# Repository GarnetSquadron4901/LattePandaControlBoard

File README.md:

# LattePanda FRC Driver Station
This is Garnet Squadron's next iteration to the control board. This one dumps the typical laptop and opts for a LattePanda Windows 10 single-board computer with Arduino Leonardo Co-Processor. This repo will hold Windows software, Arduino firmware, design files, and documentation.

## Features
- 16 20mA LED Outputs
- 16 General Purpose I/O
- 16 Analog Inputs
- 16 PWM Outputs
- Backup battery for safe shutdowns
- Auto power-on with AC connect
- LattePanda 
	- Windows 10 Professional
	- 4GB RAM
	- 64GB SSD
	- Intel Cherry Trail Z8300 Quad Core 1.8GHz
	- 3 USB Ports (2 USB 2.0, 1 USB 3.0)
	- Ethernet 10/100
	- 7" Capacitive Touch Screen (1024 x 600)
	- WiFi
	- Bluetooth

## How it works
The Arduino Leondaro connects with I/O expansion chips:

- Microchip MCP23017 - 16-Bit GPIO Expander with I2C Interface
- NXP PCA9685 - 16 channel PWM Driver
- TI CD74HC4067 Analog Multiplexer
- TI TLC59282 16-Channel Constant-Current LED Driver

There is a 2000 mAh LiPo battery that can provide backup power for an estimated 1 hour. While the battery life isn't great, the intended purpose is to provide power long enough to shutdown Windows 10 between matches. Override inputs will be available to:

- Keep the board powered on until battery life reaches ~5%
- Power button to turn on the system even when off of AC power.

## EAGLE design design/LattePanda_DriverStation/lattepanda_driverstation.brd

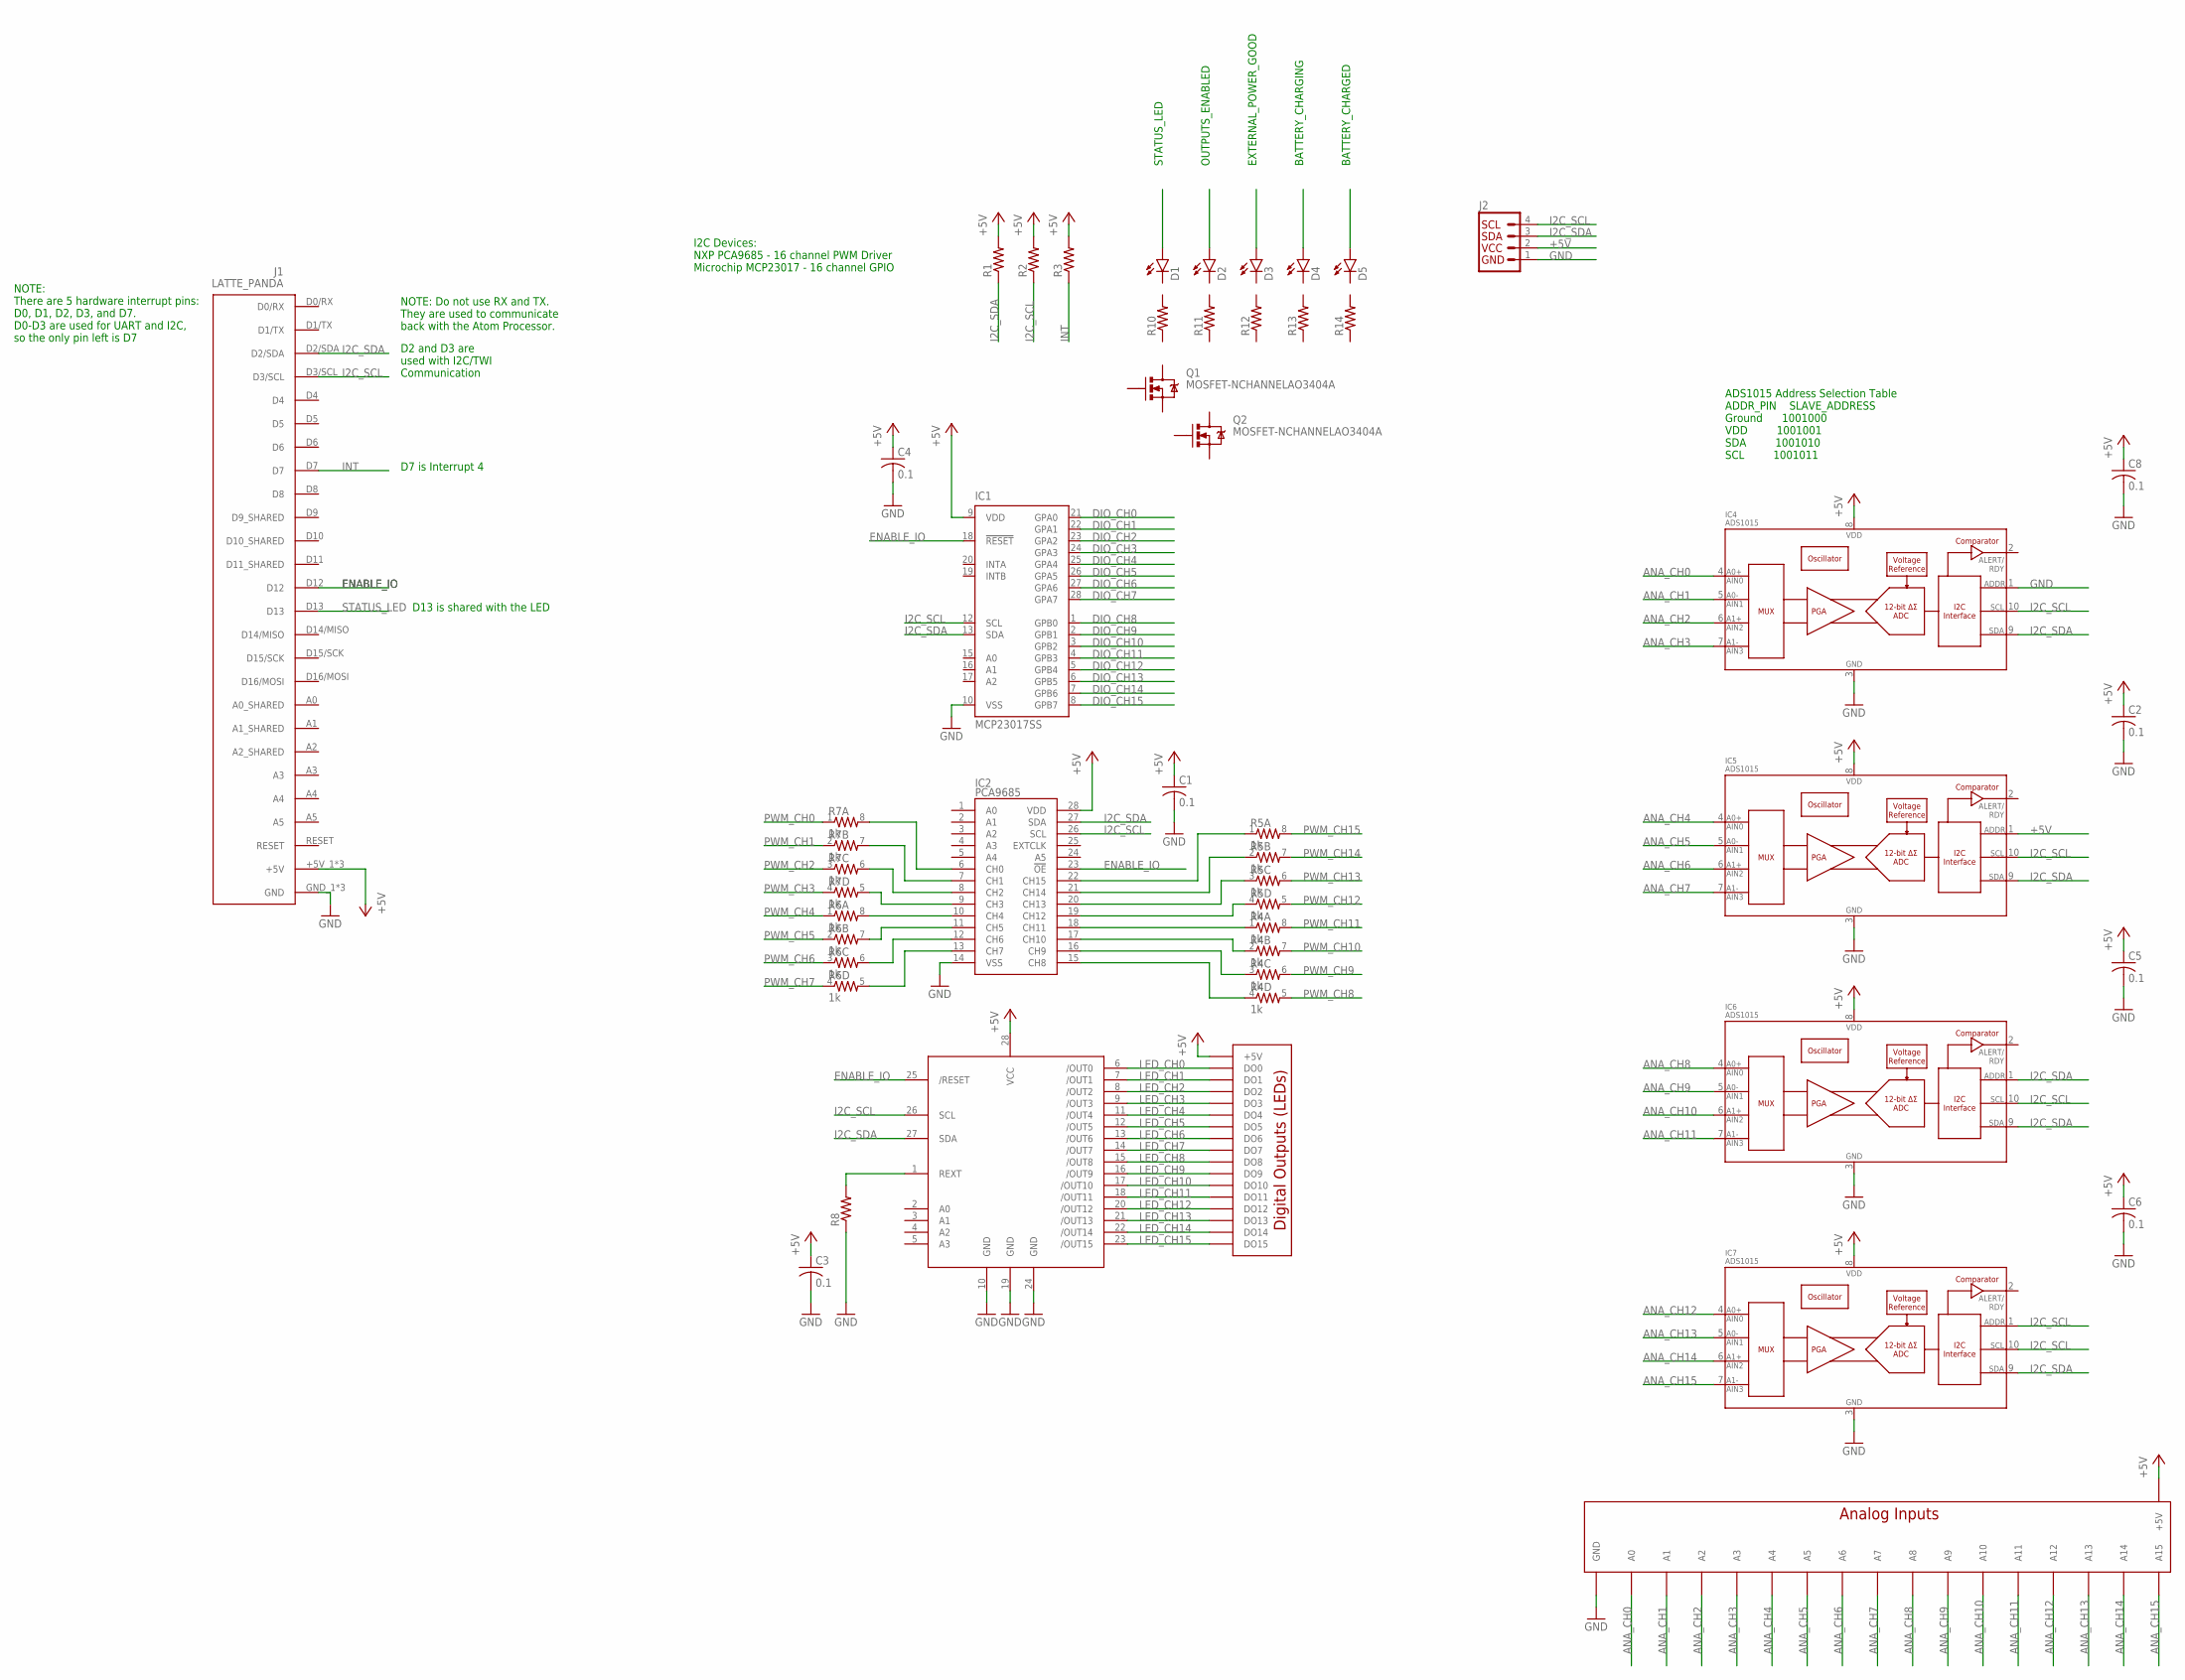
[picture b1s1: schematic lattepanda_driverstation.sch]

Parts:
C1, C2, C3, C4, C5, C6, C8: 0.1; C1206
D1, D2, D3, D4, D5: LED1206; LED-1206
IC1: MCP23017SS; SSOP28
IC2: PCA9685; TSSOP-28_4MM
IC3: TLC59116; TSSOP28
IC4, IC5, IC6, IC7: ADS1015; MSOP10
J1: LATTE_PANDA
J2: I2C_STANDARD; 1X04
Q1, Q2: MOSFET-NCHANNELAO3404A; SOT23-3
R1, R2, R3, R10, R11, R12, R13, R14: R-US_M1206; M1206
R4, R5, R6, R7: 1k; 0603-ARV
R8: R-US_R1206; R1206
U$1: ANALOGHEADER
U$2: DIGITALOUTPUTS; DIGITALOUT

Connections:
+5V: C1.1, C2.1, C3.1, C4.1, C5.1, C6.1, C8.1, IC1.9 (VDD), IC2.28 (VDD), IC3.28 (VCC), IC4.8 (VDD), IC5.1 (ADDR), IC5.8 (VDD), IC6.8 (VDD), IC7.8 (VDD), J1.+5V_1 (+5V), J1.+5V_2 (+5V), J1.+5V_3 (+5V), J2.2, R1.2, R2.2, R3.2, U$1.+5V@0 (+5V), U$1.+5V@1 (+5V), U$1.+5V@2 (+5V), U$1.+5V@3 (+5V), U$1.+5V@4 (+5V), U$1.+5V@5 (+5V), U$1.+5V@6 (+5V), U$1.+5V@7 (+5V), U$1.+5V@8 (+5V), U$1.+5V@9 (+5V), U$1.+5V@10 (+5V), U$1.+5V@11 (+5V), U$1.+5V@12 (+5V), U$1.+5V@13 (+5V), U$1.+5V@14 (+5V), U$1.+5V@15 (+5V), U$2.+5V@0 (+5V), U$2.+5V@1 (+5V), U$2.+5V@2 (+5V), U$2.+5V@3 (+5V), U$2.+5V@4 (+5V), U$2.+5V@5 (+5V), U$2.+5V@6 (+5V), U$2.+5V@7 (+5V), U$2.+5V@8 (+5V), U$2.+5V@9 (+5V), U$2.+5V@10 (+5V), U$2.+5V@11 (+5V), U$2.+5V@12 (+5V), U$2.+5V@13 (+5V), U$2.+5V@14 (+5V), U$2.+5V@15 (+5V)
ANA_CH0: IC4.4 (AIN0), U$1.0 (A0)
ANA_CH1: IC4.5 (AIN1), U$1.1 (A1)
ANA_CH2: IC4.6 (AIN2), U$1.2 (A2)
ANA_CH3: IC4.7 (AIN3), U$1.3 (A3)
ANA_CH4: IC5.4 (AIN0), U$1.4 (A4)
ANA_CH5: IC5.5 (AIN1), U$1.5 (A5)
ANA_CH6: IC5.6 (AIN2), U$1.6 (A6)
ANA_CH7: IC5.7 (AIN3), U$1.7 (A7)
ANA_CH8: IC6.4 (AIN0), U$1.8 (A8)
ANA_CH9: IC6.5 (AIN1), U$1.9 (A9)
ANA_CH10: IC6.6 (AIN2), U$1.10 (A10)
ANA_CH11: IC6.7 (AIN3), U$1.11 (A11)
ANA_CH12: IC7.4 (AIN0), U$1.12 (A12)
ANA_CH13: IC7.5 (AIN1), U$1.13 (A13)
ANA_CH14: IC7.6 (AIN2), U$1.14 (A14)
ANA_CH15: IC7.7 (AIN3), U$1.15 (A15)
DIO_CH0: IC1.21 (GPA0)
DIO_CH1: IC1.22 (GPA1)
DIO_CH2: IC1.23 (GPA2)
DIO_CH3: IC1.24 (GPA3)
DIO_CH4: IC1.25 (GPA4)
DIO_CH5: IC1.26 (GPA5)
DIO_CH6: IC1.27 (GPA6)
DIO_CH7: IC1.28 (GPA7)
DIO_CH8: IC1.1 (GPB0)
DIO_CH9: IC1.2 (GPB1)
DIO_CH10: IC1.3 (GPB2)
DIO_CH11: IC1.4 (GPB3)
DIO_CH12: IC1.5 (GPB4)
DIO_CH13: IC1.6 (GPB5)
DIO_CH14: IC1.7 (GPB6)
DIO_CH15: IC1.8 (GPB7)
ENABLE_IO: IC1.18 (!RESET), IC2.23 (!OE), IC3.25 (/RESET), J1.D12
GND: C1.2, C2.2, C3.2, C4.2, C5.2, C6.2, C8.2, IC1.10 (VSS), IC2.14 (VSS), IC3.10 (GND), IC3.19 (GND), IC3.24 (GND), IC4.1 (ADDR), IC4.3 (VSS), IC5.3 (VSS), IC6.3 (VSS), IC7.3 (VSS), J1.GND_1 (GND), J1.GND_2 (GND), J1.GND_3 (GND), J2.1, R8.1, U$1.GND@0 (GND), U$1.GND@1 (GND), U$1.GND@2 (GND), U$1.GND@3 (GND), U$1.GND@4 (GND), U$1.GND@5 (GND), U$1.GND@6 (GND), U$1.GND@7 (GND), U$1.GND@8 (GND), U$1.GND@9 (GND), U$1.GND@10 (GND), U$1.GND@11 (GND), U$1.GND@12 (GND), U$1.GND@13 (GND), U$1.GND@14 (GND), U$1.GND@15 (GND)
I2C_SCL: IC1.12 (SCL), IC2.26 (SCL), IC3.26 (SCL), IC4.10 (SCL), IC5.10 (SCL), IC6.10 (SCL), IC7.1 (ADDR), IC7.10 (SCL), J1.D3/SCL, J2.4, R2.1
I2C_SDA: IC1.13 (SDA), IC2.27 (SDA), IC3.27 (SDA), IC4.9 (SDA), IC5.9 (SDA), IC6.1 (ADDR), IC6.9 (SDA), IC7.9 (SDA), J1.D2/SDA, J2.3, R1.1
INT: J1.D7, R3.1
LED_CH0: IC3.6 (/OUT0), U$2.DO0
LED_CH1: IC3.7 (/OUT1), U$2.DO1
LED_CH2: IC3.8 (/OUT2), U$2.DO2
LED_CH3: IC3.9 (/OUT3), U$2.DO3
LED_CH4: IC3.11 (/OUT4), U$2.DO4
LED_CH5: IC3.12 (/OUT5), U$2.DO5
LED_CH6: IC3.13 (/OUT6), U$2.DO6
LED_CH7: IC3.14 (/OUT7), U$2.DO7
LED_CH8: IC3.15 (/OUT8), U$2.DO8
LED_CH9: IC3.16 (/OUT9), U$2.DO9
LED_CH10: IC3.17 (/OUT10), U$2.DO10
LED_CH11: IC3.18 (/OUT11), U$2.DO11
LED_CH12: IC3.20 (/OUT12), U$2.DO12
LED_CH13: IC3.21 (/OUT13), U$2.DO13
LED_CH14: IC3.22 (/OUT14), U$2.DO14
LED_CH15: IC3.23 (/OUT15), U$2.DO15
unnamed: IC2.6 (CH0), R7.8 (2)
unnamed: IC2.7 (CH1), R7.7 (2)
unnamed: IC2.8 (CH2), R7.6 (2)
unnamed: IC2.9 (CH3), R7.5 (2)
unnamed: IC2.10 (CH4), R6.8 (2)
unnamed: IC2.11 (CH5), R6.7 (2)
unnamed: IC2.12 (CH6), R6.6 (2)
unnamed: IC2.13 (CH7), R6.5 (2)
unnamed: IC2.15 (CH8), R4.4 (1)
unnamed: IC2.16 (CH9), R4.3 (1)
unnamed: IC2.17 (CH10), R4.2 (1)
unnamed: IC2.18 (CH11), R4.1
unnamed: IC2.19 (CH12), R5.4 (1)
unnamed: IC2.20 (CH13), R5.3 (1)
unnamed: IC2.21 (CH14), R5.2 (1)
unnamed: IC2.22 (CH15), R5.1
unnamed: IC3.1 (REXT), R8.2
PWM_CH0: R7.1
PWM_CH1: R7.2 (1)
PWM_CH2: R7.3 (1)
PWM_CH3: R7.4 (1)
PWM_CH4: R6.1
PWM_CH5: R6.2 (1)
PWM_CH6: R6.3 (1)
PWM_CH7: R6.4 (1)
PWM_CH8: R4.5 (2)
PWM_CH9: R4.6 (2)
PWM_CH10: R4.7 (2)
PWM_CH11: R4.8 (2)
PWM_CH12: R5.5 (2)
PWM_CH13: R5.6 (2)
PWM_CH14: R5.7 (2)
PWM_CH15: R5.8 (2)
STATUS_LED: J1.D13

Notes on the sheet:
NOTE: Do not use RX and TX. They are used to communicate back with the Atom Processor.
D13 is shared with the LED
D2 and D3 are used with I2C/TWI Communication
D7 is Interrupt 4
NOTE: There are 5 hardware interrupt pins: D0, D1, D2, D3, and D7. D0-D3 are used for UART and I2C, so the only pin left is D7
I2C Devices: NXP PCA9685 - 16 channel PWM Driver Microchip MCP23017 - 16 channel GPIO
STATUS_LED
OUTPUTS_ENABLED
EXTERNAL_POWER_GOOD
BATTERY_CHARGING
BATTERY_CHARGED
ADS1015 Address Selection Table ADDR_PIN SLAVE_ADDRESS Ground 1001000 VDD 1001001 SDA 1001010 SCL 1001011

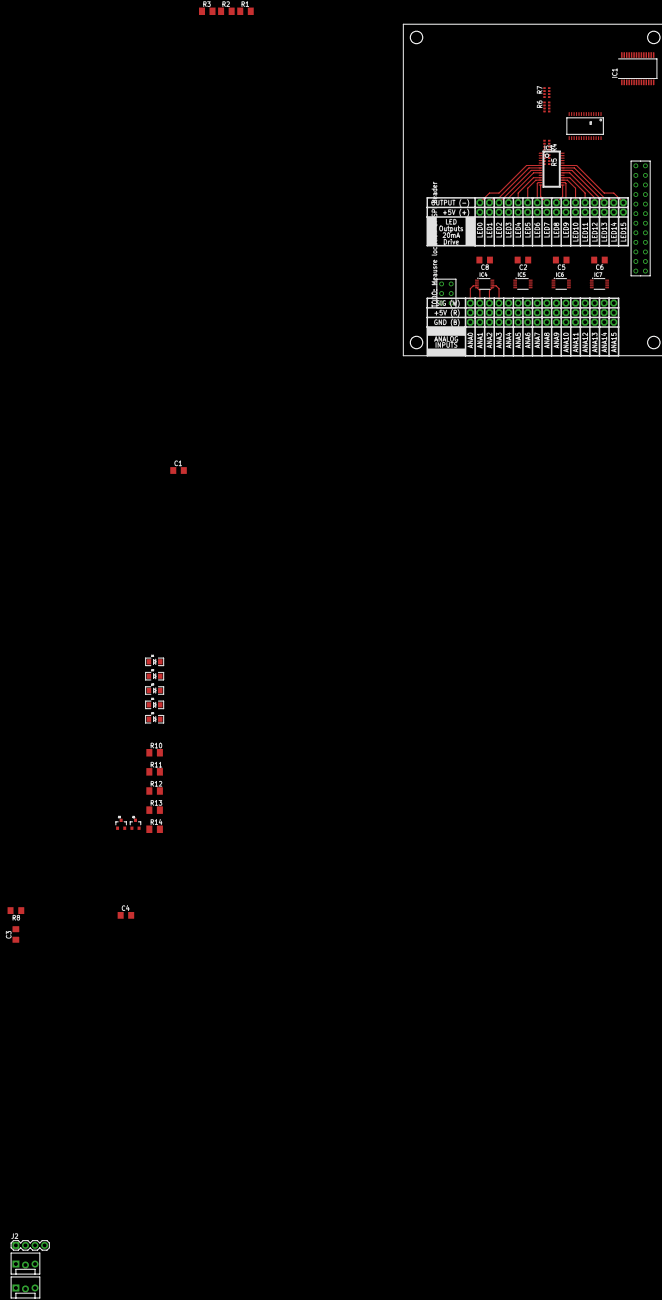
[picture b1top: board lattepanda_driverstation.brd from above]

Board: 2 copper layers, 40 parts (0 on the bottom side), 55 nets.

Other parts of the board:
J3: TEMP_SENSE; MOLEX-1X3_LOCK
J4: FAN_OUT; MOLEX-1X3_LOCK

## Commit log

2016-05-31 Added some documentation.
2016-06-01 Added start of board design.
2016-06-03 Progress made on the schematic.
2016-06-05 Progress commit.

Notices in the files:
parts and their libraries:
SparkFun-AnalogIC: Licensing:Creative Commons ShareAlike 4.0 International - https://creativecommons.org/licenses/by-sa/4.0
